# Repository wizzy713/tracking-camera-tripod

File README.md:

# CamX - Automated Tripod Tracking System

CamX is a technical Android application designed to interface with motorized tripod hardware. It provides real-time subject localization using on-device computer vision and transmits precision tracking coordinates to external hardware via low-latency network protocols.

## System Features

- Three Detection Modes: Face (default), whole Body (MediaPipe pose model, with a skeleton overlay) or Ball, toggled per-session.
- Hand Gestures: Raise an open palm to lock the tracker onto the nearest detected subject in a crowd (or resume), a closed fist to stop auto tracking, a victory sign to start/stop recording. Each can be switched off in Advanced Settings.
- Predictive Tracking: Implements a 1D Kalman Filter (one instance per axis) to estimate subject velocity and predict trajectory coordinates.
- Resolution-Independent Localization: Transmits a normalized X/Y error in [-1, 1] to the hardware layer, decoupled from camera resolution and orientation.
- Connectivity: Manual IP/port configuration to link with tripod hardware on the local Wi-Fi network.
- Manual Joystick (Advanced Settings): An on-screen joystick drives pan/tilt directly, for framing a shot or testing the rig without a subject.
- Auto Zoom (Advanced Settings): Adjusts the camera zoom to keep the tracked subject at a chosen size in the frame.
- Experiment Tab: Live-tunes the firmware's PID gains and the app's Kalman filter/prediction horizon against a running rig, and labels CSV logging sessions with test metadata -- see [TESTING.md](./TESTING.md) for suggested experiments.
- Diagnostic Tools: Includes connection testing with custom payloads and telemetry logging in CSV format, including per-frame tracking error (`ErrX`/`ErrY`).
- Battery Readout: The tripod's INA219 fuel gauge streams pack state of charge back over the same UDP link; the camera screen shows a live battery indicator (%, voltage, colour-coded).
- Comprehensive Camera Control: Provides high-resolution photo capture, video recording with audio, and hardware flip capabilities.

## Architecture and Workflow

### 1. Localization Algorithm
The localization process follows a multi-stage pipeline:
- Frame Acquisition: Frames are captured via CameraX; analysis resolution is device-dependent (not pinned).
- Subject Identification: One of three selectable modes locates the subject -- ML Kit Face Detection (default), whole-body detection (MediaPipe Pose Landmarker, falling back to the EfficientDet-Lite0 COCO model filtered to "person"), or Ball Detection (colour segmentation, falling back to the same COCO model filtered to "sports ball"; used for the pendulum test in TESTING.md) -- see ARCHITECTURE.md.
- Gesture Recognition: MediaPipe Hand Landmarker identifies an open palm (lock/resume), a closed fist (stop tracking) and a victory sign (record).
- Normalized Error Calculation: The bounding box center is converted to a normalized X/Y error in [-1, 1] relative to frame center, in the rotation-corrected upright frame.
- Trajectory Estimation: A Kalman Filter per axis processes the coordinates to filter noise and predict the subject's position a configurable horizon (~200ms default) into the future -- live-tunable, along with the filter's noise constants, from the Experiment tab.

### 2. Communication Protocol
- Hardware Link: UDP (User Datagram Protocol) is utilized for minimum latency transmission.
- Payload Format: "EX:[FLOAT],EY:[FLOAT],SEQ:[UINT]" -- normalized error per axis plus a sequence number for loss/reorder detection.
- Reverse Telemetry: The firmware replies on the same socket with "BATT:[%],MV:[mV],MA:[mA],WH:[Wh]" every ~2s for the on-screen battery indicator, and with "CFG:KP:...,KI:...,KD:...,MS:...,DZ:..." immediately after any PID-gain set/query from the Experiment tab.
- Configuration: The IP address and port of the ESP32 are entered manually in the connection settings.

## Project Structure

- MainActivity.kt: Central controller managing application state, UI composition, and hardware coordination.
- ExperimentScreen.kt: Live PID/Kalman tuning UI and labeled test-run logging.
- KalmanFilter.kt: Mathematical implementation for state estimation and trajectory prediction.
- UdpSender.kt: Managed network worker for asynchronous hardware command transmission.
- LogManager.kt: Utility for persistent CSV-based telemetry recording.

## Setup Requirements

- Hardware: ESP32-based microcontroller with servo motor integration, plus an INA219 sensor on the battery for charge monitoring. See [firmware folder](./firmware) for details.
- Network: Android device and ESP32 must reside on the same subnet.
- Configuration: Tripod parameters (IP and Port) are managed via the in-app connection settings.
- AI Assets: Ensure hand_landmarker.task, pose_landmarker_lite.task and efficientdet_lite0.tflite are present in the assets folder.

## Dependencies

- Android Jetpack CameraX (v1.4.1)
- Google ML Kit Face Detection; MediaPipe Object Detector (ball mode)
- MediaPipe Tasks Vision (v0.10.14)
- Android Jetpack Compose (Material 3)
- Kotlin Coroutines for asynchronous processing

## Testing

See [TESTING.md](./TESTING.md) for the suggested evaluation protocol (step response,
pendulum swing at varied heights/velocities, occlusion/coast, deadzone jitter, and
end-to-end latency measurement), built around the Experiment tab and the CSV's `ErrX`/
`ErrY` tracking-error columns.

## License
Educational and hobbyist use only.

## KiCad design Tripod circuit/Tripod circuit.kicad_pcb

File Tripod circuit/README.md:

# CamX Tripod Carrier Board (rev A)

A two-layer carrier board (160 x 62 mm) that replaces the jumper-wire power and signal wiring
of the tripod. Open `Tripod circuit.kicad_pro` in KiCad 7 or later.

**Status: first draft, not fabricated or tested.** The schematic and PCB were generated by
script and autorouted (Freerouting). KiCad's design rule check reports no clearance errors and
no unconnected pads, and the PCB netlist matches the schematic. Review the items under
"Check before ordering" first.

## What it changes, and why

| Problem on the current rig | What the board does |
|---|---|
| ESP32 browned out and dropped Wi-Fi when the servos moved; everything shared one 5 V regulator | One 5 V / 3 A buck regulator per servo (U2, U3), each with its own input, output and servo-side bulk capacitors. The ESP32's 5 V is taken through a Schottky diode (D3) with its own 470 uF hold-up capacitor (C9), so a servo dip cannot pull it down |
| The INA219 module's 0.1 ohm shunt and jumper contacts starved the regulator | INA219 on the board with a 10 mOhm shunt (R2), Kelvin-connected through a 10 R / 100 nF input filter (R8, R9, C13) |
| Miswiring the INA219 destroyed an ESP32 board | Fixed traces, a reverse-polarity MOSFET on the battery input (Q1), and a 6.3 A fuse (F1) |
| Nothing stops the tilt axis driving into its end stop | Two limit-switch inputs (J7, J8) on GPIO10 and GPIO11 |
| No power switch | Terminal J2 for an external switch in series with the battery (rated 6 A or more) |

Also on the board: I2C expansion header (J9), power LED (D4), four M3 mounting holes, and a
copper keep-out under the DevKit's antenna.

## Test points

Loop test points for a multimeter or scope clip, each labelled on the silkscreen:

| Test point | Net | Expect |
|---|---|---|
| TP1 `VRAW` | Battery at the input terminal, before the fuse and switch | 6.0-8.4 V |
| TP2 `VBAT` | Battery after the fuse, switch, MOSFET and shunt (regulator input) | within about 0.1 V of TP1 under load |
| TP3 `5V PAN` | Pan servo regulator output | 5.0 V |
| TP4 `5V TILT` | Tilt servo regulator output | 5.0 V |
| TP5 `5V LOG` | ESP32 5 V supply, after the isolation diode | about 4.7 V |
| TP6 `GND` | Ground reference | 0 V |

The difference between TP1 and TP2 under load is the drop across the whole protection chain.

## Signals

| Function | ESP32-C6 pin | Notes |
|---|---|---|
| Pan servo PWM | GPIO2 | via 220 R (R5) to J5 pin 3 |
| Tilt servo PWM | GPIO3 | via 220 R (R6) to J6 pin 3 |
| I2C SDA / SCL | GPIO6 / GPIO7 | INA219 at 0x40, 4k7 pull-ups to 3V3 |
| Limit switch up / down | GPIO10 / GPIO11 | switch to GND, use the internal pull-up |

These match `firmware/camx_tripod/camx_tripod.ino`. Servo headers are GND, +5 V, signal.

## Firmware changes this board needs

- **INA219 calibration.** The Adafruit library's default calibration assumes a 0.1 ohm shunt.
  With 10 mOhm the reported current is ten times too low until the calibration (or a x10
  scale factor) is changed.
- **Limit switches.** The firmware does not read GPIO10/11 yet.

## Bill of materials

| Ref | Value | Footprint | Qty |
|---|---|---|---|
| U2, U3 | LM2596S-5.0 | TO-263-5 | 2 |
| L1, L2 | 33 uH, 4 A | 12 x 12 mm SMD | 2 |
| D1, D2 | SS54 Schottky | SMC | 2 |
| C2, C3, C6 | 470 uF 16 V | radial 10 mm, 5 mm pitch | 3 |
| C4, C7 | 470 uF 10 V low-ESR | radial 10 mm | 2 |
| C5, C8, C9 | 470 uF 10 V | radial 10 mm | 3 |
| U1 | INA219AIDR | SOIC-8 | 1 |
| R2 | 10 mOhm 1 % 2 W | 2512 | 1 |
| Q1 | AOD4185 P-MOSFET | TO-252 (DPAK) | 1 |
| D3 | SS14 Schottky | SMA | 1 |
| D4 | green LED | 0805 | 1 |
| F1 | 6.3 A, 5 x 20 mm fuse and holder | Schurter 0031.8201 | 1 |
| J1, J2 | 2-way screw terminal, 5.08 mm | Phoenix MKDS 1,5 | 2 |
| J3, J4 | 1 x 16 socket, 2.54 mm | pin socket | 2 |
| J5, J6 | 1 x 3 header | 2.54 mm | 2 |
| J7, J8 | 1 x 2 header | 2.54 mm | 2 |
| J9 | 1 x 4 header | 2.54 mm | 1 |
| C1, C10, C11, C12, C13 | 100 nF | 0805 | 5 |
| R1 | 100 k | 0805 | 1 |
| R3, R4 | 4k7 | 0805 | 2 |
| R5, R6 | 220 R | 0805 | 2 |
| R7 | 1 k | 0805 | 1 |
| R8, R9 | 10 R | 0805 | 2 |
| TP1-TP6 | loop test point | 2.5 mm loop, 1.0 mm drill | 6 |

## Check before ordering

1. **DevKit pinout and row spacing.** J3/J4 assume an ESP32-C6-DevKitC-1: two rows of 16
   pins, 22.86 mm apart, with the pin order on the schematic. Measure your board and compare
   its silkscreen pin by pin; other ESP32-C6 boards differ.
2. **Screw terminal orientation.** Confirm in the 3D viewer that the wire entries of J1 and J2
   face the board edge, and rotate them if not.
3. **Regulator headroom.** The LM2596 needs about 1.3 V more than its output at full load, so
   the 5 V rails start to sag below a pack voltage of roughly 6.5 V. The MG996R runs down to
   4.8 V, so this costs speed, not function.
4. **Current rating.** Battery-path traces are 1.5 mm and servo-rail traces 1.0 mm, the widest
   the autorouter could fit between the regulator pins. In 1 oz copper that suits the rig's
   normal draw but runs warm at the 6.3 A fuse rating or a sustained 3 A servo stall. Order
   2 oz copper, or widen the long runs by hand.
5. **Regulator layout.** The autorouter does not know that the input capacitor, regulator and
   diode of a buck converter should form a tight loop. It works at the LM2596's 150 kHz, but
   tidying that loop by hand will reduce noise.
6. **Library notices.** A design rule check run without KiCad's footprint libraries configured
   lists 52 "footprint does not match library" notices; they are not layout errors.

The schematic uses net labels rather than drawn wires between blocks. `Tripod circuit
schematic.pdf`, `board-front.png` and `board-back.png` are exports of this revision.

## Production files

`production/` was generated with the Fabrication Toolkit plugin (bennymeg/Fabrication-Toolkit),
using its JLCPCB rotation corrections:

- `Tripod_circuit.zip` -- gerbers and drill files, ready to upload
- `bom.csv` -- bill of materials in JLCPCB's format
- `positions.csv` -- component placement file
- `designators.csv`, `netlist.ipc`

The "LCSC Part #" column in `bom.csv` is empty: no LCSC part numbers have been chosen. It only
matters if JLCPCB assembles the board; fill it in after picking parts that are in stock.
Regenerate these files after any change to the board.

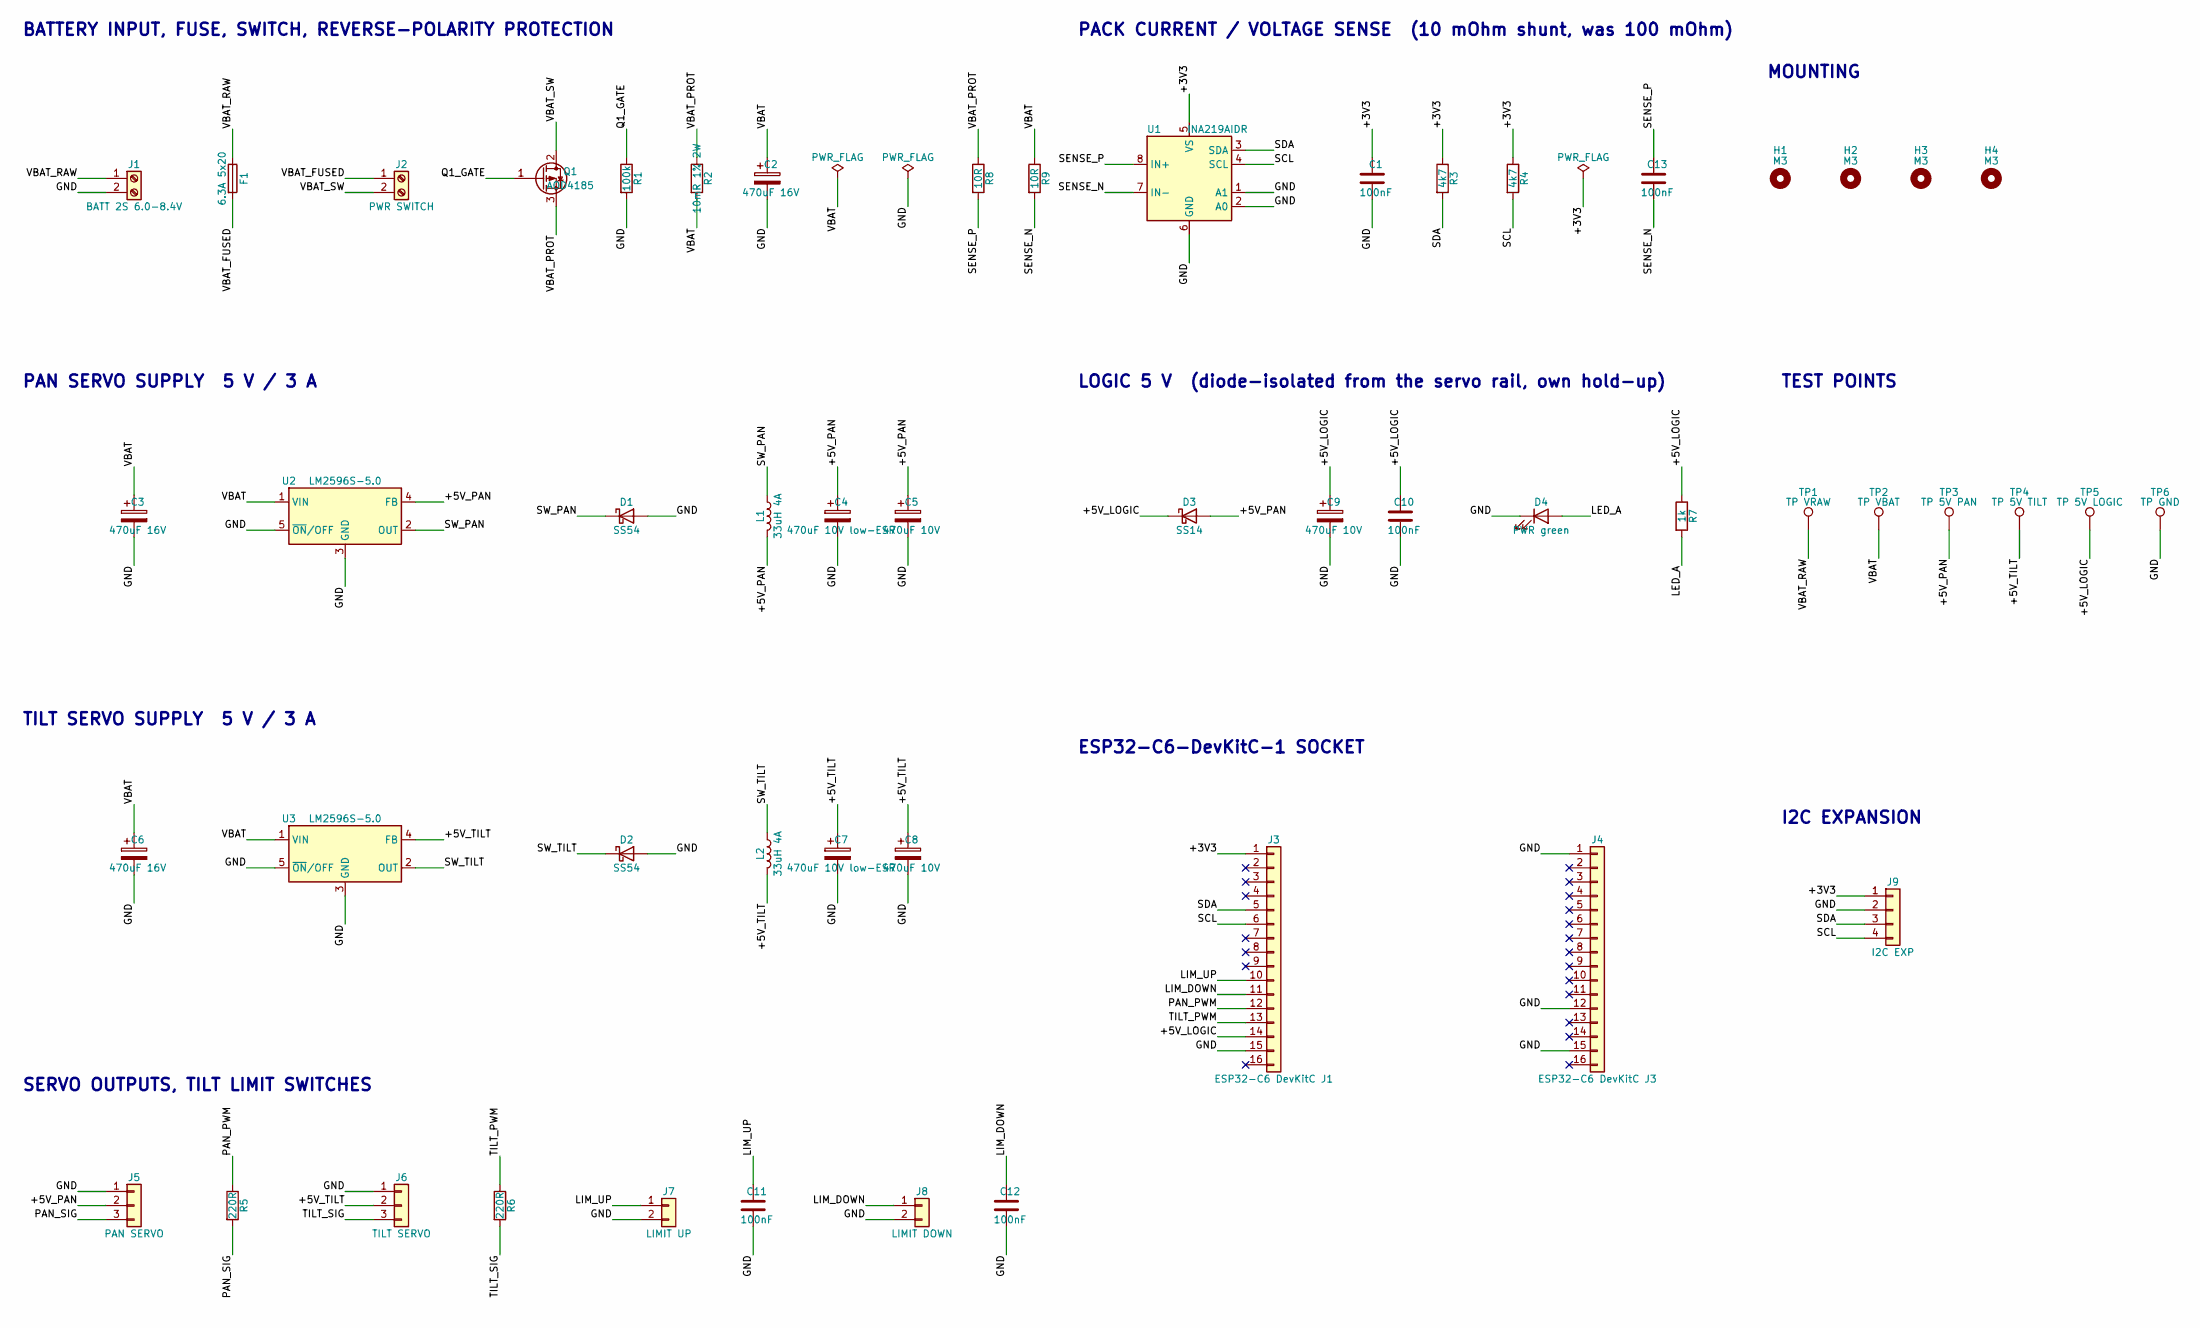
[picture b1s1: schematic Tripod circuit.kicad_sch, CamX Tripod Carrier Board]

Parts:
C1, C10, C11, C12, C13: 100nF; C_0805_2012Metric
C2, C3, C6: 470uF 16V; CP_Radial_D10.0mm_P5.00mm
C4, C7: 470uF 10V low-ESR; CP_Radial_D10.0mm_P5.00mm
C5, C8, C9: 470uF 10V; CP_Radial_D10.0mm_P5.00mm
D1, D2: SS54; D_SMC
D3: SS14; D_SMA
D4: PWR green; LED_0805_2012Metric
F1: 6.3A 5x20; Fuseholder_Cylinder-5x20mm_Schurter_0031_8201_Horizontal_Op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
H1, H2, H3, H4: M3; MountingHole_3.2mm_M3
J1: BATT 2S 6.0-8.4V; TerminalBlock_Phoenix_MKDS-1,5-2-5.08_1x02_P5.08mm_Horizont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
J2: PWR SWITCH; TerminalBlock_Phoenix_MKDS-1,5-2-5.08_1x02_P5.08mm_Horizont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
J3: ESP32-C6 DevKitC J1; PinSocket_1x16_P2.54mm_Vertical
J4: ESP32-C6 DevKitC J3; PinSocket_1x16_P2.54mm_Vertical
J5: PAN SERVO; PinHeader_1x03_P2.54mm_Vertical
J6: TILT SERVO; PinHeader_1x03_P2.54mm_Vertical
J7: LIMIT UP; PinHeader_1x02_P2.54mm_Vertical
J8: LIMIT DOWN; PinHeader_1x02_P2.54mm_Vertical
J9: I2C EXP; PinHeader_1x04_P2.54mm_Vertical
L1, L2: 33uH 4A; L_12x12mm_H8mm
Q1: AOD4185; TO-252-2
R1: 100k; R_0805_2012Metric
R2: 10mR 1% 2W; R_2512_6332Metric
R3, R4: 4k7; R_0805_2012Metric
R5, R6: 220R; R_0805_2012Metric
R7: 1k; R_0805_2012Metric
R8, R9: 10R; R_0805_2012Metric
TP1: TP VRAW; TestPoint_Loop_D2.50mm_Drill1.0mm
TP2: TP VBAT; TestPoint_Loop_D2.50mm_Drill1.0mm
TP3: TP 5V PAN; TestPoint_Loop_D2.50mm_Drill1.0mm
TP4: TP 5V TILT; TestPoint_Loop_D2.50mm_Drill1.0mm
TP5: TP 5V LOGIC; TestPoint_Loop_D2.50mm_Drill1.0mm
TP6: TP GND; TestPoint_Loop_D2.50mm_Drill1.0mm
U1: INA219AIDR; SOIC-8_3.9x4.9mm_P1.27mm
U2, U3: LM2596S-5.0; TO-263-5_TabPin3

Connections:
+3V3: C1.1, J3.1, J9.1, R3.1, R4.1, U1.5 (VS)
+5V_LOGIC: C9.1, C10.1, D3.1 (K), J3.14, R7.1, TP5.1
+5V_PAN: C4.1, C5.1, D3.2 (A), J5.2, L1.2, TP3.1, U2.4 (FB)
+5V_TILT: C7.1, C8.1, J6.2, L2.2, TP4.1, U3.4 (FB)
GND: C1.2, C2.2, C3.2, C4.2, C5.2, C6.2, C7.2, C8.2, C9.2, C10.2, C11.2, C12.2, D1.2 (A), D2.2 (A), D4.1 (K), J1.2, J3.15, J4.1, J4.12, J4.15, J5.1, J6.1, J7.2, J8.2, J9.2, R1.2, TP6.1, U1.1 (A1), U1.2 (A0), U1.6 (GND), U2.3 (GND), U2.5 (~ON/OFF), U3.3 (GND), U3.5 (~ON/OFF)
LED_A: D4.2 (A), R7.2
LIM_DOWN: C12.1, J3.11, J8.1
LIM_UP: C11.1, J3.10, J7.1
PAN_PWM: J3.12, R5.1
PAN_SIG: J5.3, R5.2
Q1_GATE: Q1.1 (G), R1.1
SCL: J3.6, J9.4, R4.2, U1.4 (SCL)
SDA: J3.5, J9.3, R3.2, U1.3 (SDA)
SENSE_N: C13.2, R9.2, U1.7 (IN-)
SENSE_P: C13.1, R8.2, U1.8 (IN+)
SW_PAN: D1.1 (K), L1.1, U2.2 (OUT)
SW_TILT: D2.1 (K), L2.1, U3.2 (OUT)
TILT_PWM: J3.13, R6.1
TILT_SIG: J6.3, R6.2
VBAT: C2.1, C3.1, C6.1, R2.2, R9.1, TP2.1, U2.1 (VIN), U3.1 (VIN)
VBAT_FUSED: F1.2, J2.1
VBAT_PROT: Q1.3 (S), R2.1, R8.1
VBAT_RAW: F1.1, J1.1, TP1.1
VBAT_SW: J2.2, Q1.2 (D)

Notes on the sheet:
TEST POINTS
BATTERY INPUT, FUSE, SWITCH, REVERSE-POLARITY PROTECTION
PACK CURRENT / VOLTAGE SENSE (10 mOhm shunt, was 100 mOhm)
PAN SERVO SUPPLY 5 V / 3 A
TILT SERVO SUPPLY 5 V / 3 A
LOGIC 5 V (diode-isolated from the servo rail, own hold-up)
ESP32-C6-DevKitC-1 SOCKET
SERVO OUTPUTS, TILT LIMIT SWITCHES
I2C EXPANSION
MOUNTING

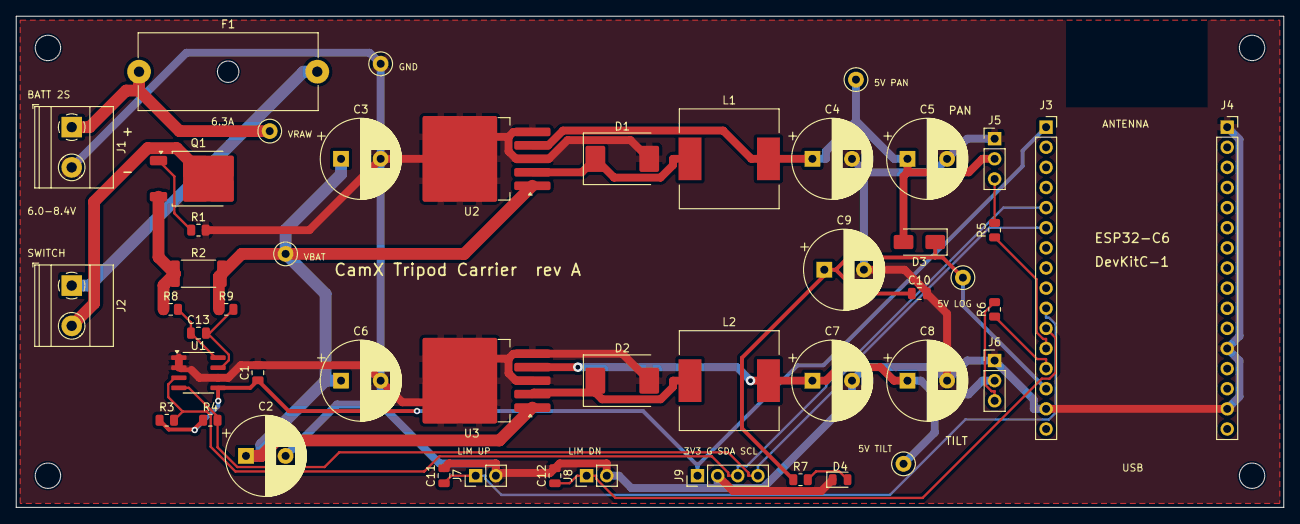
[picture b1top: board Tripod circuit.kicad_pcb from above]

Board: 2 copper layers, 160.0 x 62.0 mm, 52 parts (0 on the bottom side), 24 nets.

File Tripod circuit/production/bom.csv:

Designator,Footprint,Quantity,Value,LCSC Part #
"C1, C10, C11, C12, C13",0805,5,100nF,
"C2, C3, C6",CP_Radial_D10.0mm_P5.00mm,3,470uF 16V,
"C4, C7",CP_Radial_D10.0mm_P5.00mm,2,470uF 10V low-ESR,
"C5, C8, C9",CP_Radial_D10.0mm_P5.00mm,3,470uF 10V,
"D1, D2",D_SMC,2,SS54,
D3,D_SMA,1,SS14,
D4,0805,1,PWR green,
F1,Fuseholder_Cylinder-5x20mm_Schurter_0031_8201_Horizontal_Open,1,6.3A 5x20,
J1,"TerminalBlock_Phoenix_MKDS-1,5-2-5.08_1x02_P5.08mm_Horizontal",1,BATT 2S 6.0-8.4V,
J2,"TerminalBlock_Phoenix_MKDS-1,5-2-5.08_1x02_P5.08mm_Horizontal",1,PWR SWITCH,
J3,PinSocket_1x16_P2.54mm_Vertical,1,ESP32-C6 DevKitC J1,
J4,PinSocket_1x16_P2.54mm_Vertical,1,ESP32-C6 DevKitC J3,
J5,PinHeader_1x03_P2.54mm_Vertical,1,PAN SERVO,
J6,PinHeader_1x03_P2.54mm_Vertical,1,TILT SERVO,
J7,PinHeader_1x02_P2.54mm_Vertical,1,LIMIT UP,
J8,PinHeader_1x02_P2.54mm_Vertical,1,LIMIT DOWN,
J9,PinHeader_1x04_P2.54mm_Vertical,1,I2C EXP,
"L1, L2",L_12x12mm_H8mm,2,33uH 4A,
Q1,TO-252-2,1,AOD4185,
R1,0805,1,100k,
R2,2512,1,10mR 1% 2W,
"R3, R4",0805,2,4k7,
"R5, R6",0805,2,220R,
R7,0805,1,1k,
"R8, R9",0805,2,10R,
TP1,TestPoint_Loop_D2.50mm_Drill1.0mm,1,TP VRAW,
TP2,TestPoint_Loop_D2.50mm_Drill1.0mm,1,TP VBAT,
TP3,TestPoint_Loop_D2.50mm_Drill1.0mm,1,TP 5V PAN,
TP4,TestPoint_Loop_D2.50mm_Drill1.0mm,1,TP 5V TILT,
TP5,TestPoint_Loop_D2.50mm_Drill1.0mm,1,TP 5V LOGIC,
TP6,TestPoint_Loop_D2.50mm_Drill1.0mm,1,TP GND,
U1,SOIC-8_3.9x4.9mm_P1.27mm,1,INA219AIDR,
"U2, U3",TO-263-5_TabPin3,2,LM2596S-5.0,
